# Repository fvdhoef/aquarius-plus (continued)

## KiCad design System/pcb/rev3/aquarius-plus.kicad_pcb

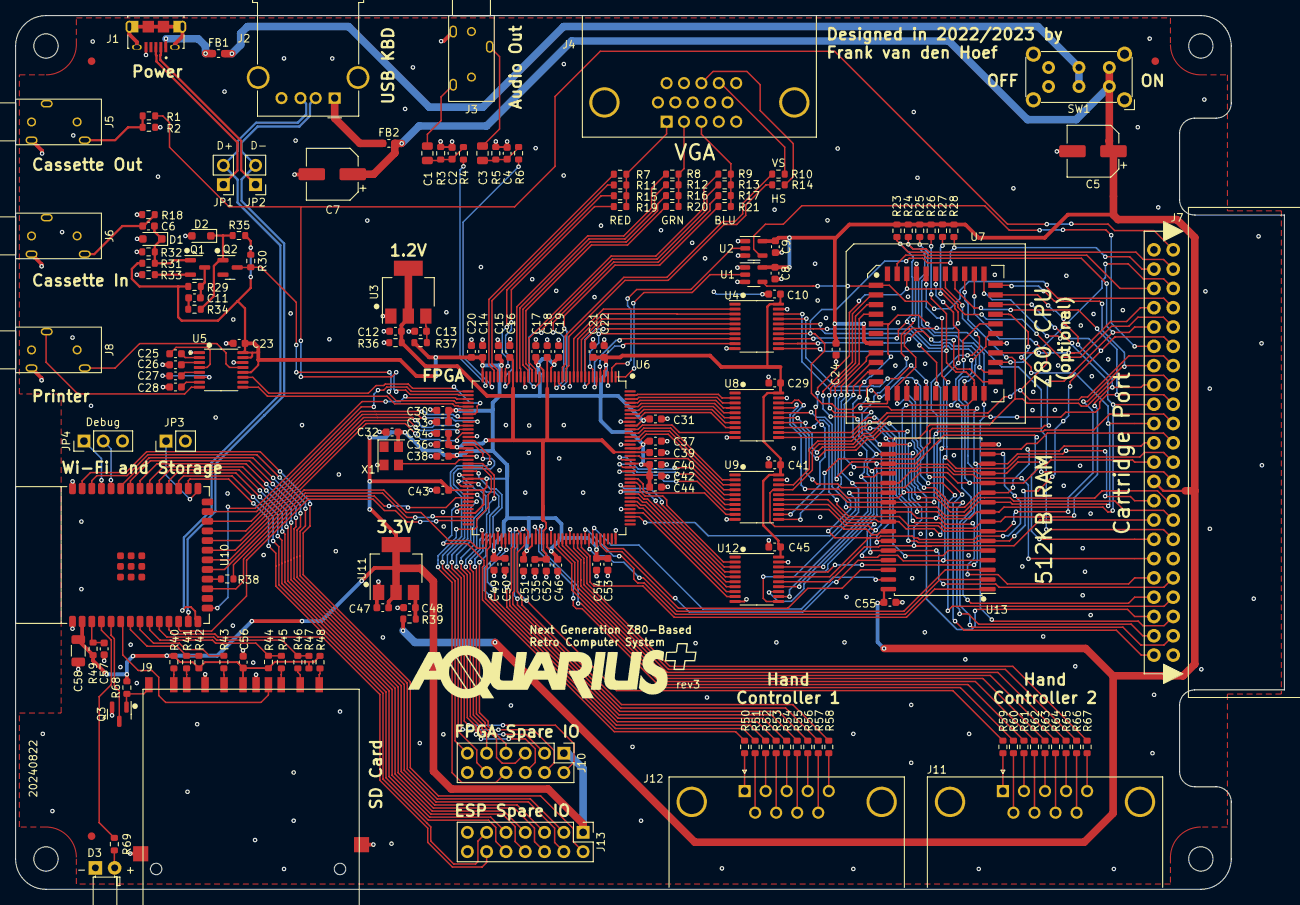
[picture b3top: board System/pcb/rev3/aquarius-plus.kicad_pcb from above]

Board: 2 copper layers, 167.0 x 115.0 mm, 173 parts (0 on the bottom side), 226 nets.

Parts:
C1, C3: 10uF; C_0805_2012Metric
C2, C4, C6, C8, C9, C10, C14, C15, C16, C17, C18, C19, C22, C24, C25, C26, C27, C28, C29, C30, C31, C32, C36, C37, C38, C39, C40, C41, C42, C43, C45, C46, C49, C51, C52, C54, C55, C57: 100nF; C_0603_1608Metric
C5, C7: 100uF; CP_Elec_6.3x7.7
C11, C12, C13, C20, C21, C23, C33, C34, C35, C44, C47, C48, C50, C53, C56: 4.7uF; C_0603_1608Metric
C58: 22uF; C_1206_3216Metric
D1, D2: 1N4148WS; D_SOD-323_HandSoldering
D3: SD act.; LED_D3.0mm_Horizontal_O1.27mm_Z2.0mm
FB1, FB2: 220; L_0603_1608Metric
FID1, FID2, FID3: Fiducial; Fiducial_1mm_Mask2mm
H1, H2, H3, H4: MountingHole; MountingHole_3.2mm_M3
J1: Power in; AMPHENOL_10118194-0001LF
J2: ESP USB Host; USB_A_Molex_67643_Horizontal
J3: Audio out; C2939180
J4: VGA; ICD15S13E4GV00LF
J5: Cassette out; C2939180
J6: Cassette in; C2939180
J7: Expansion port; CR22A-44D-2.54DSA(70)
J8: Printer; C2939180
J9: TF-03A
J10: FPGA spare; PinHeader_2x06_P2.54mm_Vertical
J11: Hand controller 2; DSUB-9_Male_Horizontal_P2.77x2.84mm_EdgePinOffset9.90mm_Hou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
J12: Hand controller 1; DSUB-9_Male_Horizontal_P2.77x2.84mm_EdgePinOffset9.90mm_Hou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
J13: ESP32 spare; PinHeader_2x07_P2.54mm_Vertical
JP1, JP2: USB; PinHeader_1x02_P2.54mm_Vertical
JP3: Bootloader; PinHeader_1x02_P2.54mm_Vertical
JP4: DBG; PinHeader_1x03_P2.54mm_Vertical
Q1, Q2: BC847C; SOT-23
Q3: 2N7002; SOT-23
R1, R40, R42, R44, R47, R48, R49, R68: 10k; R_0603_1608Metric
R2, R36, R41, R43, R45, R46, R50, R51, R52, R53, R54, R55, R56, R57, R58, R59, R60, R61, R62, R63, R64, R65, R66, R67: 100; R_0603_1608Metric
R3, R5: 150; R_0603_1608Metric
R4, R6: 330; R_0603_1608Metric
R7, R8, R9: 536; R_0603_1608Metric
R10, R14: 820; R_0603_1608Metric
R11, R12, R13: 1070; R_0603_1608Metric
R15, R16, R17: 2150; R_0603_1608Metric
R18: 82; R_0603_1608Metric
R19, R20, R21: 4300; R_0603_1608Metric
R23, R24, R25, R26, R27, R28: 1k; R_0603_1608Metric
R29, R30: 4.7k; R_0603_1608Metric
R31: 220k; R_0603_1608Metric
R32, R35: 47k; R_0603_1608Metric
R33, R38, R69: 220; R_0603_1608Metric
R34: 2.2k; R_0603_1608Metric
R37, R39: 1; R_0603_1608Metric
SW1: SW_DPDT_x2; SW_E-Switch_EG2219_DPDT_Angled
U1, U2: SN74AHCT1G125DBVR; SOT-23-5
U3: LD1117S12; SOT-223-3_TabPin2
U4, U8, U9, U12: SN74CB3T3245PWR; TSSOP-20_4.4x6.5mm_P0.65mm
U5: MAX3221ECPWR; TSSOP-16_4.4x5mm_P0.65mm
U6: XC6SLX9-2TQG144C; TQFP-144_20x20mm_P0.5mm
U7: Z84C3008VEG; PLCC-44_SMD-Socket
U10: ESP32-S3-WROOM-1-N4R2; ESP32-S2-SOLO-N4R2
U11: LDL1117S33R; SOT-223-3_TabPin2
U13: IS61C5128AS-25QLI; SSOP-32_11.305x20.495mm_P1.27mm
X1: SX3M14.31818M20F30TNN; Oscillator_SMD_SeikoEpson_SG8002CE-4Pin_3.2x2.5mm

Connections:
+1V2: C12.1, C16.1, C18.1, C34.1, C35.1, C36.1, C39.1, C52.1, R36.2, U3.2 (VO), U6.19 (VCCINT), U6.28 (VCCINT), U6.52 (VCCINT), U6.89 (VCCINT), U6.128 (VCCINT)
+3V3: C10.1, C14.1, C15.1, C17.1, C19.1, C20.1, C21.1, C22.1, C23.1, C29.1, C30.1, C31.1, C32.1, C33.1, C37.1, C38.1, C40.1, C41.1, C42.1, C43.1, C44.1, C45.1, C46.1, C47.1, C49.1, C50.1, C51.1, C53.1, C54.1, C56.1, C58.1, J9.4 (VDD), J10.1, J13.1, R29.2, R30.2, R31.2, R35.2, R37.1, R40.2, R42.2, R44.2, R47.2, R48.2, R49.1, R68.2, U4.20 (VCC), U5.12 (FORCEON), U5.15 (VCC), U5.16 (~FORCEOFF), U6.4 (VCCO_3), U6.18 (VCCO_3), U6.20 (VCCAUX), U6.31 (VCCO_3), U6.36 (VCCAUX), U6.42 (VCCO_2), U6.53 (VCCAUX), U6.60 (B2_IO_M1), U6.63 (VCCO_2), U6.69 (B2_IO_M0), U6.76 (VCCO_1), U6.86 (VCCO_1), U6.90 (VCCAUX), U6.103 (VCCO_1), U6.122 (VCCO_0), U6.125 (VCCO_0), U6.129 (VCCAUX), U6.135 (VCCO_0), U8.20 (VCC), U9.20 (VCC), U10.2 (3V3), U11.2 (VO), U12.20 (VCC), X1.4 (VCC)
+5V: C5.1, C7.1, C8.1, C9.1, C24.1, C55.1, FB2.2, J7.25, R23.1, R24.1, R25.1, R26.1, R27.1, R28.1, R39.1, SW1.1 (A), SW1.4 (A), U1.5 (VCC), U2.5 (VCC), U7.13 (+5V), U13.32 (VDD)
/USB_D+: J1.3 (D+), JP1.1 (A)
/USB_D-: J1.2 (D-), JP2.1 (A)
A0: J7.23, U7.34 (A0), U8.18 (B1), U13.12 (A0)
A1: J7.21, U7.35 (A1), U8.17 (B2), U13.11 (A1)
A2: J7.19, U7.36 (A2), U8.16 (B3), U13.10 (A2)
A3: J7.17, U7.37 (A3), U8.15 (B4), U13.9 (A3)
A4: J7.15, U7.38 (A4), U8.14 (B5), U13.8 (A4)
A5: J7.13, U7.39 (A5), U8.13 (B6), U13.7 (A5)
A6: J7.12, U7.40 (A6), U8.12 (B7), U13.6 (A6)
A7: J7.14, U7.41 (A7), U8.11 (B8), U13.5 (A7)
A8: J7.16, U7.42 (A8), U9.18 (B1), U13.27 (A8)
A9: J7.18, U7.43 (A9), U9.17 (B2), U13.26 (A9)
A10: J7.20, U7.44 (A10), U9.16 (B3), U13.23 (A10)
A11: J7.22, U7.1 (A11), U9.15 (B4), U13.25 (A11)
A12: J7.24, U7.2 (A12), U9.14 (B5), U13.4 (A12)
A13: J7.36, U7.3 (A13), U9.13 (B6), U13.28 (A13)
A14: J7.10, U7.4 (A14), U9.12 (B7)
A15: J7.9, U7.5 (A15), U9.11 (B8)
AUDIO_L: R4.1, U6.35 (B3_IO)
AUDIO_R: R6.1, U6.34 (B3_IO_VREF)
BA14: U6.101 (B1_IO), U13.3 (A14)
BA15: U6.102 (B1_IO), U13.31 (A15)
BA16: U6.100 (B1_IO), U13.2 (A16)
BA17: U6.99 (B1_IO), U13.1 (A17)
BA18: U6.104 (B1_IO_VREF), U13.30 (A18)
BUSACK#: J7.42, R26.2, U4.11 (B8), U7.27 (~BUSACK)
BUSREQ#: J7.4, R24.2, U4.12 (B7), U7.29 (~BUSREQ)
CART_CE#: J7.11, U2.4
CASSETTE_IN: Q2.3 (C), R30.1, U6.40 (B2_IO)
CASSETTE_OUT: J7.2, R1.1, U6.38 (B2_IO)
D0: J7.26, U7.16 (D0), U12.18 (B1), U13.13 (DQ0)
D1: J7.27, U7.17 (D1), U12.17 (B2), U13.14 (DQ1)
D2: J7.28, U7.14 (D2), U12.16 (B3), U13.15 (DQ2)
D3: J7.29, U7.9 (D3), U12.15 (B4), U13.17 (DQ3)
D4: J7.30, U7.8 (D4), U12.14 (B5), U13.18 (DQ4)
D5: J7.31, U7.10 (D5), U12.13 (B6), U13.19 (DQ5)
D6: J7.32, U7.11 (D6), U12.12 (B7), U13.20 (DQ6)
D7: J7.33, U7.15 (D7), U12.11 (B8), U13.21 (DQ7)
ESP_CTS: U6.44 (B2_IO), U10.24 (IO47)
ESP_EXP0: J13.2, U10.39 (IO1)
ESP_EXP1: J13.3, U10.38 (IO2)
ESP_EXP2: J13.4, U10.35 (IO42)
ESP_EXP3: J13.5, U10.34 (IO41)
ESP_EXP4: J13.6, U10.33 (IO40)
ESP_EXP5: J13.7, U10.32 (IO39)
ESP_EXP6: J13.8, U10.31 (IO38)
ESP_EXP7: J13.9, U10.30 (IO37)
ESP_EXP8: J13.10, U10.29 (IO36)
ESP_EXP9: J13.11, U10.28 (IO35)
ESP_EXP10: J13.12, U10.11 (IO18)
ESP_NOTIFY: U6.48 (B2_IO), U10.20 (IO12)
ESP_RTS: U6.46 (B2_IO), U10.22 (IO14)
ESP_RX: U6.45 (B2_IO), U10.23 (IO21)
ESP_TX: U6.47 (B2_IO_VREF), U10.21 (IO13)
ESP_USB_D+: J2.3 (D+), JP1.2 (B), U10.14 (IO20/USB_DP)
ESP_USB_D-: J2.2 (D-), JP2.2 (B), U10.13 (IO19/USB_DM)
FPGA_A0: U6.143 (B0_IO_VREF), U8.2 (A1)
FPGA_A1: U6.142 (B0_IO), U8.3 (A2)
FPGA_A2: U6.141 (B0_IO), U8.4 (A3)
FPGA_A3: U6.140 (B0_IO), U8.5 (A4)
FPGA_A4: U6.139 (B0_IO), U8.6 (A5)
FPGA_A5: U6.138 (B0_IO), U8.7 (A6)
FPGA_A6: U6.137 (B0_IO), U8.8 (A7)
FPGA_A7: U6.134 (B0_IO_GCLK19), U8.9 (A8)
FPGA_A8: U6.133 (B0_IO_GCLK18), U9.2 (A1)
FPGA_A9: U6.132 (B0_IO_GCLK17), U9.3 (A2)
FPGA_A10: U6.131 (B0_IO_GCLK16), U9.4 (A3)
FPGA_A11: U6.127 (B0_IO_GCLK15), U9.5 (A4)
FPGA_A12: U6.126 (B0_IO_GCLK14), U9.6 (A5)
FPGA_A13: U6.124 (B0_IO_GCLK13), U9.7 (A6)
FPGA_A14: U6.123 (B0_IO_GCLK12), U9.8 (A7)
FPGA_A15: U6.121 (B0_IO), U9.9 (A8)
FPGA_BUSACK#: U4.9 (A8), U6.5 (B3_IO)
FPGA_BUSREQ#: U4.8 (A7), U6.6 (B3_IO)
FPGA_CART_CE#: U2.2, U6.2 (B3_IO)
FPGA_D0: U6.120 (B0_IO_VREF), U12.2 (A1)
FPGA_D1: U6.119 (B0_IO), U12.3 (A2)
FPGA_D2: U6.118 (B0_IO), U12.4 (A3)
FPGA_D3: U6.117 (B0_IO), U12.5 (A4)
FPGA_D4: U6.116 (B0_IO), U12.6 (A5)
FPGA_D5: U6.115 (B0_IO), U12.7 (A6)
FPGA_D6: U6.114 (B0_IO), U12.8 (A7)
FPGA_D7: U6.112 (B0_IO), U12.9 (A8)
FPGA_DONE: U6.71 (DONE), U10.12 (IO8)
FPGA_EXP0: J10.2, U6.66 (B2_IO)
FPGA_EXP1: J10.3, U6.64 (B2_IO)
FPGA_EXP2: J10.4, U6.62 (B2_IO)
FPGA_EXP3: J10.5, U6.61 (B2_IO)
FPGA_EXP4: J10.6, U6.59 (B2_IO)
FPGA_EXP5: J10.7, U6.58 (B2_IO)
FPGA_EXP6: J10.8, U6.57 (B2_IO)
FPGA_EXP7: J10.9, U6.56 (B2_IO_GCLK1)
FPGA_EXP8: J10.10, U6.51 (B2_IO_GCLK31)
FPGA_EXP9: J10.11, U6.50 (B2_IO_GCLK30)
FPGA_INT#: U4.6 (A5), U6.8 (B3_IO)
FPGA_IORQ#: U4.3 (A2), U6.11 (B3_IO)
FPGA_MREQ#: U4.2 (A1), U6.12 (B3_IO)
FPGA_PHI: U1.2, U6.1 (B3_IO)
FPGA_PROG#: U6.37 (PROG_B), U10.25 (IO48)
FPGA_RD#: U4.4 (A3), U6.10 (B3_IO)
FPGA_RESET#: U4.7 (A6), U6.7 (B3_IO)
FPGA_WR#: U4.5 (A4), U6.9 (B3_IO)
GND: C2.2, C4.2, C5.2, C7.2, C8.2, C9.2, C10.2, C12.2, C13.2, C14.2, C15.2, C16.2, C17.2, C18.2, C19.2, C20.2, C21.2, C22.2, C23.2, C24.2, C26.2, C28.2, C29.2, C30.2, C31.2, C32.2, C33.2, C34.2, C35.2, C36.2, C37.2, C38.2, C39.2, C40.2, C41.2, C42.2, C43.2, C44.2, C45.2, C46.2, C47.2, C48.2, C49.2, C50.2, C51.2, C52.2, C53.2, C54.2, C55.2, C56.2, C57.2, C58.2, D1.2 (A), D2.2 (A), D3.1 (K), J1.5 (GND), J1.6 (Shield), J2.4 (GND), J2.5 (Shield), J3.S, J4.0, J4.5, J4.6, J4.7, J4.8, J4.10, J5.S, J6.S, J7.34, J7.44, J8.S, J9.3 (VSS), J9.6 (VSS), J9.12 (SHELL1), J9.13 (SHELL2), J10.12, J11.0 (PAD), J12.0 (PAD), J13.13, J13.14, JP3.2 (B), JP4.3, Q2.2 (E), Q3.2 (S), R2.1, R3.1, R5.1, R18.1, R32.1, R33.1, R36.1, U1.1, U1.3 (GND), U2.1, U2.3 (GND), U3.1 (GND), U4.10 (GND), U4.19 (~OE), U5.1 (~EN), U5.14 (GND), U6.3 (GND), U6.13 (GND), U6.25 (GND), U6.49 (GND), U6.54 (GND), U6.68 (GND), U6.73 (SUSPEND), U6.77 (GND), U6.91 (GND), U6.96 (GND), U6.108 (GND), U6.113 (GND), U6.130 (GND), U6.136 (GND), U7.33 (GND), U8.10 (GND), U8.19 (~OE), U9.10 (GND), U9.19 (~OE), U10.1 (GND), U10.40 (GND), U10.41 (EPAD), U11.1 (GND), U12.10 (GND), U12.19 (~OE), U13.16 (GND), X1.2 (GND)
HALT#: J7.41, U7.20 (~HALT)
HC1_D00: R51.2, U6.75 (B1_IO_AWAKE)
HC1_D01: R53.2, U6.79 (B1_IO)
HC1_D02: R55.2, U6.81 (B1_IO)
HC1_D03: R57.2, U6.83 (B1_IO)
HC1_D04: R58.2, U6.84 (B1_IO_GCLK4)
HC1_D05: R56.2, U6.82 (B1_IO)
HC1_D06: R54.2, U6.80 (B1_IO)
HC1_D07: R52.2, U6.78 (B1_IO)
HC1_D08: R50.2, U6.67 (B2_IO)
HC2_D00: R60.2, U6.87 (B1_IO_GCLK6)
HC2_D01: R62.2, U6.92 (B1_IO_GCLK8)
HC2_D02: R64.2, U6.94 (B1_IO_GCLK10)
HC2_D03: R66.2, U6.97 (B1_IO)
HC2_D04: R67.2, U6.98 (B1_IO)
HC2_D05: R65.2, U6.95 (B1_IO_GCLK11)
HC2_D06: R63.2, U6.93 (B1_IO_GCLK9)
HC2_D07: R61.2, U6.88 (B1_IO_GCLK7)
HC2_D08: R59.2, U6.85 (B1_IO_GCLK5)
INT#: J7.3, R28.2, U4.14 (B5), U7.18 (~INT)
IORQ#: J7.43, U4.17 (B2), U7.22 (~IORQ)
M1#: J7.6, U7.31 (~M1)
MREQ#: J7.38, U4.18 (B1), U7.21 (~MREQ)
NMI#: J7.39, R27.2, U7.19 (~NMI)
unnamed: C1.1, C2.1, R3.2, R4.2
unnamed: C1.2, J3.T
unnamed: C3.1, C4.1, R5.2, R6.2
unnamed: C3.2, J3.R
unnamed: C6.1, J6.T, R18.2
unnamed: C11.2, R34.1
unnamed: C6.2, D1.1 (K), Q1.1 (B), R31.1, R32.2
unnamed: D2.1 (K), Q2.1 (B), R34.2, R35.1
unnamed: D3.2 (A), R69.2
unnamed: FB1.1, J1.1 (VBUS)
unnamed: FB2.1, J2.1 (VBUS)
unnamed: J4.1, R7.2, R11.2, R15.2, R19.2
unnamed: J4.2, R8.2, R12.2, R16.2, R20.2
unnamed: J4.3, R9.2, R13.2, R17.2, R21.2
unnamed: J4.13, R14.2
unnamed: J4.14, R10.2
unnamed: J5.T, R1.2, R2.2
unnamed: J9.1 (CD/DAT3), R46.2
unnamed: J9.5 (CLK), R43.2
unnamed: J9.2 (CMD), R45.2
unnamed: J9.7 (DAT0), R41.2
unnamed: J9.8 (DAT1), R40.1
unnamed: J9.9 (DAT2), R48.1
unnamed: J9.11 (WRITE_PROTECT), Q3.1 (G), R68.1
unnamed: J11.1, R59.1
unnamed: J11.2, R61.1
unnamed: J11.3, R63.1
unnamed: J11.4, R65.1
unnamed: J11.5, R67.1
unnamed: J11.6, R60.1
unnamed: J11.7, R62.1
unnamed: J11.8, R64.1
unnamed: J11.9, R66.1
unnamed: J12.1, R50.1
unnamed: J12.2, R52.1
unnamed: J12.3, R54.1
unnamed: J12.4, R56.1
unnamed: J12.5, R58.1
unnamed: J12.6, R51.1
unnamed: J12.7, R53.1
unnamed: J12.8, R55.1
unnamed: J12.9, R57.1
unnamed: JP3.1 (A), U10.27 (IO0)
unnamed: JP4.1, U10.37 (IO43/TXD0)
unnamed: JP4.2, U10.36 (IO44/RXD0)
unnamed: C11.1, Q1.3 (C), R29.1
unnamed: Q1.2 (E), R33.2
unnamed: C13.1, R37.2, U3.3 (VI)
unnamed: C25.1, U5.2 (C1+)
unnamed: C25.2, U5.4 (C1-)
unnamed: C27.1, U5.5 (C2+)
unnamed: C27.2, U5.6 (C2-)
unnamed: J8.T, U5.13 (DOUT)
unnamed: J8.R, U5.8 (RIN)
unnamed: C26.1, U5.3 (V+)
unnamed: C28.1, U5.7 (V-)
unnamed: R38.2, U6.70 (B2_IO_CCLK)
unnamed: C57.1, R49.2, U10.3 (EN)
unnamed: C48.1, R39.2, U11.3 (VI)
PHI: J7.8, U1.4, U7.7 (CLK)
PRINTER_IN: U5.9 (ROUT), U6.41 (B2_IO)
PRINTER_OUT: U5.11 (DIN), U6.43 (B2_IO)
RAM_CE#: U6.111 (B0_IO), U13.22 (~CE)
RAM_WE#: U6.105 (B1_IO), U13.29 (~WE)
RD#: J7.35, U4.16 (B3), U7.23 (~RD), U13.24 (~OE)
RESET#: J7.5, R23.2, U4.13 (B6), U7.30 (~RESET)
RFSH#: J7.7, U7.32 (~RFSH)
SD_ACTIVITY: R69.1, U10.4 (IO4)
SD_CD: J9.10 (CARD_DETECT), U10.6 (IO6)
SD_MISO: R41.1, R42.1, U10.7 (IO7)
SD_MOSI: R44.1, R45.1, U10.9 (IO16)
SD_SCK: R43.1, U10.8 (IO15)
SD_SSEL#: R46.1, R47.1, U10.10 (IO17)
SD_WP#: Q3.3 (D), U10.5 (IO5)
SPI_CS#: U6.39 (B2_IO_INIT_B), U10.15 (IO3)
SPI_MISO: U6.74 (B2_IO_DOUT), U10.19 (IO11)
SPI_MOSI: U6.65 (B2_IO_DIN), U10.17 (IO9)
SPI_SCLK: R38.1, U10.18 (IO10)
SYSCLK: U6.55 (B2_IO_GCLK0), X1.3 (OUT)
VBUS: FB1.2, SW1.2 (B), SW1.5 (B)
VGA_B0: R21.1, U6.16 (B3_IO_GCLK22)
VGA_B1: R17.1, U6.17 (B3_IO_GCLK23)
VGA_B2: R13.1, U6.21 (B3_IO_GCLK24)
VGA_B3: R9.1, U6.22 (B3_IO_GCLK25)
VGA_G0: R20.1, U6.23 (B3_IO_GCLK26)
VGA_G1: R16.1, U6.24 (B3_IO_GCLK27)
VGA_G2: R12.1, U6.26 (B3_IO)
VGA_G3: R8.1, U6.27 (B3_IO)
VGA_HSYNC: R14.1, U6.14 (B3_IO_GCLK20)
VGA_R0: R19.1, U6.29 (B3_IO)
VGA_R1: R15.1, U6.30 (B3_IO)
VGA_R2: R11.1, U6.32 (B3_IO)
VGA_R3: R7.1, U6.33 (B3_IO)
VGA_VSYNC: R10.1, U6.15 (B3_IO_GCLK21)
WAIT#: J7.40, R25.2, U7.28 (~WAIT)
WR#: J7.37, U4.15 (B4), U7.26 (~WR)

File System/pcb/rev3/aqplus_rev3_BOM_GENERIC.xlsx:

Id | Designator | Footprint | Quantity | Designation | MFG | MFG PN | Mouser Part | Comments
1 | C21,C47,C35,C20,C56,C48,C33,C23,C53,C11,C13,C50,C12,C44,C34 | C_0603_1608Metric | 15 | 4.7uF | Kyocera | 06033D475KAT2A | 581-06033D475KAT2A
2 | R66,R53,R64,R54,R46,R59,R58,R57,R51,R36,R60,R56,R43,R65,R62,R61,R45,R2,R50,R55,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 | R_0603_1608Metric | 24 | 100 | Bourns | CHP0603AFX-1000ELF | 652-CHP0603AFX1000EL
3 | J7 | CR22A-44D-2.54DSA(70) | 1 | Expansion port | Hirose Electric | CR22A-44D-2.54DSA(70) | 798-CR22A44D254DSA70
4 | R24,R25,R23,R27,R26,R28 | R_0603_1608Metric | 6 | 1k | Bourns | CHP0603QFX-1001ELF | 652-CHP0603QFX-1001E
5 | R49,R47,R1,R44,R40,R68,R42,R48 | R_0603_1608Metric | 8 | 10k | TE Connectivity | CRGP0603F10K | 279-CRGP0603F10K
6 | U5 | TSSOP-16_4.4x5mm_P0.65mm | 1 | MAX3221ECPWR | TI | MAX3221ECPWR | 595-MAX3221ECPWR
7 | U13 | SSOP-32_11.305x20.495mm_P1.27mm | 1 | IS61C5128AS-25QLI | ISSI | IS61C5128AS-25QLI | 870-61C5128AS-25QLI
8 | JP3 | PinHeader_1x02_P2.54mm_Vertical | 1 | Bootloader | Harwin | M20-9990246 | 855-M20-9990246
9 | R20,R21,R19 | R_0603_1608Metric | 3 | 4300 | Vishay | CRCW06034K30FKEA | 71-CRCW0603-4.3K-E3
10 | R13,R11,R12 | R_0603_1608Metric | 3 | 1070 | Vishay | CRCW06031K07FKEA | 71-CRCW0603-1.07K-E3
11 | C46,C4,C52,C55,C19,C45,C25,C26,C41,C30,C15,C40,C29,C42,C49,C57,C24,C37,C39,C14,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 | C_0603_1608Metric | 38 | 100nF | TDK | C0603X5R1E104K030BB | 810-C0603X5R1E104KBB
12 | J11 | DSUB-9_Male_Horizontal_P2.77x2.84mm_EdgePinOffset9.90mm_Housed_MountingHolesOff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 | 1 | Hand controller 2 | Amphenol | D09P23A4GV00LF | 649-D09P23A4GV00LF
13 | U3 | SOT-223-3_TabPin2 | 1 | LD1117S12 | STMicroelectronics | LD1117S12CTR | 511-LD1117S12CTR
14 | U6 | TQFP-144_20x20mm_P0.5mm | 1 | XC6SLX9-2TQG144C | Xilinx | XC6SLX9-2TQG144C | 217-XC6SLX9-2TQG144C
15 | H4,H3,H1,H2 | MountingHole_3.2mm_M3 | 4 | MountingHole | - | - | - | DNP
16 | R15,R16,R17 | R_0603_1608Metric | 3 | 2150 | Vishay | CRCW06032K15FKTA | 71-CRCW0603-2.15K
17 | JP1,JP2 | PinHeader_1x02_P2.54mm_Vertical | 2 | USB | Harwin | M20-9990246 | 855-M20-9990246
18 | C3,C1 | C_0805_2012Metric | 2 | 10uF | Kyocera | 0805YC106KAT2A | 581-0805YC106KAT2A
19 | R30,R29 | R_0603_1608Metric | 2 | 4.7k | Vishay | 71-RCG0603220RJNEA | 71-CRCW0603J-4.7K-E3
20 | Q2,Q1 | SOT-23 | 2 | BC847C | Diotech Semiconductor | BC847C | 637-BC847C
21 | R4,R6 | R_0603_1608Metric | 2 | 330 | Yageo | AR0603JR-07330RL | 603-AR0603JR-07330RL
22 | J6 | C2884998 | 1 | Cassette in | Switchcraft | 35RASMT2BHNTRX | 502-35RASMT2BHNTRX
23 | J10 | PinHeader_2x06_P2.54mm_Vertical | 1 | FPGA spare | - | - | - | DNP
24 | R33,R69,R38 | R_0603_1608Metric | 3 | 220 | Vishay | RCG0603220RJNEA | 71-RCG0603220RJNEA
25 | SW1 | SW_E-Switch_EG2219_DPDT_Angled | 1 | SW_DPDT_x2 | E-Switch | EG2219 | 612-EG2219
26 | R14,R10 | R_0603_1608Metric | 2 | 820 | TE Connectivity | CRG0603F820R | 279-CRG0603F820R
27 | R39,R37 | R_0603_1608Metric | 2 | 1 | Bourns | CHP0603QFW-1R00ELF | 652-CHP0603QFW-1R00E
28 | R9,R7,R8 | R_0603_1608Metric | 3 | 536 | Bourns | CR0603-FX-5360ELF | 652-CR0603FX-5360ELF
29 | R3,R5 | R_0603_1608Metric | 2 | 150 | TE Connectivity | CRG0603F150R | 279-CRG0603F150R
30 | JP4 | PinHeader_1x03_P2.54mm_Vertical | 1 | DBG | Harwin | M22-2510305 | 855-M22-2510305
31 | R34 | R_0603_1608Metric | 1 | 2.2k | Vishay | CRCW06032K20JNEA | 71-CRCW0603J-2.2K-E3
32 | J1 | AMPHENOL_10118194-0001LF | 1 | Power in | Amphenol | 10118194-0001LF | 649-10118194-0001LF
33 | U11 | SOT-223-3_TabPin2 | 1 | LDL1117S33R | STMicroelectronics | LDL1117S33R | 511-LDL1117S33R
34 | R31 | R_0603_1608Metric | 1 | 220k | Yageo | AC0603FR-10220KL | 603-AC0603FR-10220KL
35 | J13 | PinHeader_2x07_P2.54mm_Vertical | 1 | ESP32 spare | - | - | - | DNP
36 | J8 | C2884998 | 1 | Printer | Switchcraft | 35RASMT2BHNTRX | 502-35RASMT2BHNTRX
37 | R32,R35 | R_0603_1608Metric | 2 | 47k | Yageo | RC0603FR-0747KL | 603-RC0603FR-0747KL
38 | J9 | TF-03A | 1 | SD Card Connector | Amphenol | GSD090012SEU | 523-GSD090012SEU
39 | U2,U1 | SOT-23-5 | 2 | SN74AHCT1G125DBVR | TI | SN74AHCT1G125DBVR | 595-SNAHCT1G125DBVR
40 | U7 | LQFP-44_10x10mm_P0.8mm | 1 | Z84C0010AEG | Zilog | Z84C0010AEG | 692-Z84C0010AEG
41 | J4 | ICD15S13E4GV00LF | 1 | VGA | Amphenol | ICD15S13E4GV00LF | 649-ICD15S13E4GV00LF
42 | U4,U9,U8,U12 | TSSOP-20_4.4x6.5mm_P0.65mm | 4 | SN74CB3T3245PWR | TI | SN74CB3T3245PWR | 595-SN74CB3T3245PWR
43 | J2 | USB_A_Molex_67643_Horizontal | 1 | ESP USB Host | Molex | 67643-0910 | 538-67643-0910
44 | D3 | LED_D3.0mm_Horizontal_O1.27mm_Z2.0mm | 1 | SD act. | Lumex | SSL-LX3054USBD | 696-SSL-LX3054USBD
45 | C7,C5 | CP_Elec_6.3x7.7 | 2 | 100uF | Panasonic | EEE-HC0J101P | 667-EEE-HC0J101P
46 | D2,D1 | D_SOD-323_HandSoldering | 2 | 1N4148WS | Diodes Incorporated | 1N4148WS-7-F | 621-1N4148WS-F
47 | X1 | Oscillator_SMD_SeikoEpson_SG8002CE-4Pin_3.2x2.5mm | 1 | SX3M14.31818M20F30TNN | Abracon | ASE-14.31818MHZ-LC-T | 815-ASE14.31818MLCT
48 | C58 | C_1206_3216Metric | 1 | 22uF | Kyocera | 1206YD226MAT2A | 581-1206YD226MAT2A
49 | J3 | C2884998 | 1 | Audio out | Switchcraft | 35RASMT2BHNTRX | 502-35RASMT2BHNTRX
50 | J12 | DSUB-9_Male_Horizontal_P2.77x2.84mm_EdgePinOffset9.90mm_Housed_MountingHolesOff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 | 1 | Hand controller 1 | Amphenol | D09P23A4GV00LF | 649-D09P23A4GV00LF
51 | U10 | ESP32-S2-SOLO-N4R2 | 1 | ESP32-S3-WROOM-1-N4R2 | Espressif Systems | ESP32-S3-WROOM-1-N4R2 | 356-ESP32S3WROM1N4R2
52 | Q3 | SOT-23 | 1 | 2N7002 | Comchip Technology | A2N7002H-HF | 750-A2N7002H-HF
53 | J5 | C2884998 | 1 | Cassette out | Switchcraft | 35RASMT2BHNTRX | 502-35RASMT2BHNTRX
54 | R31 | R_0603_1608Metric | 1 | 82 | Yageo | AR0603JR-0782RL | 603-AR0603JR-0782RL
